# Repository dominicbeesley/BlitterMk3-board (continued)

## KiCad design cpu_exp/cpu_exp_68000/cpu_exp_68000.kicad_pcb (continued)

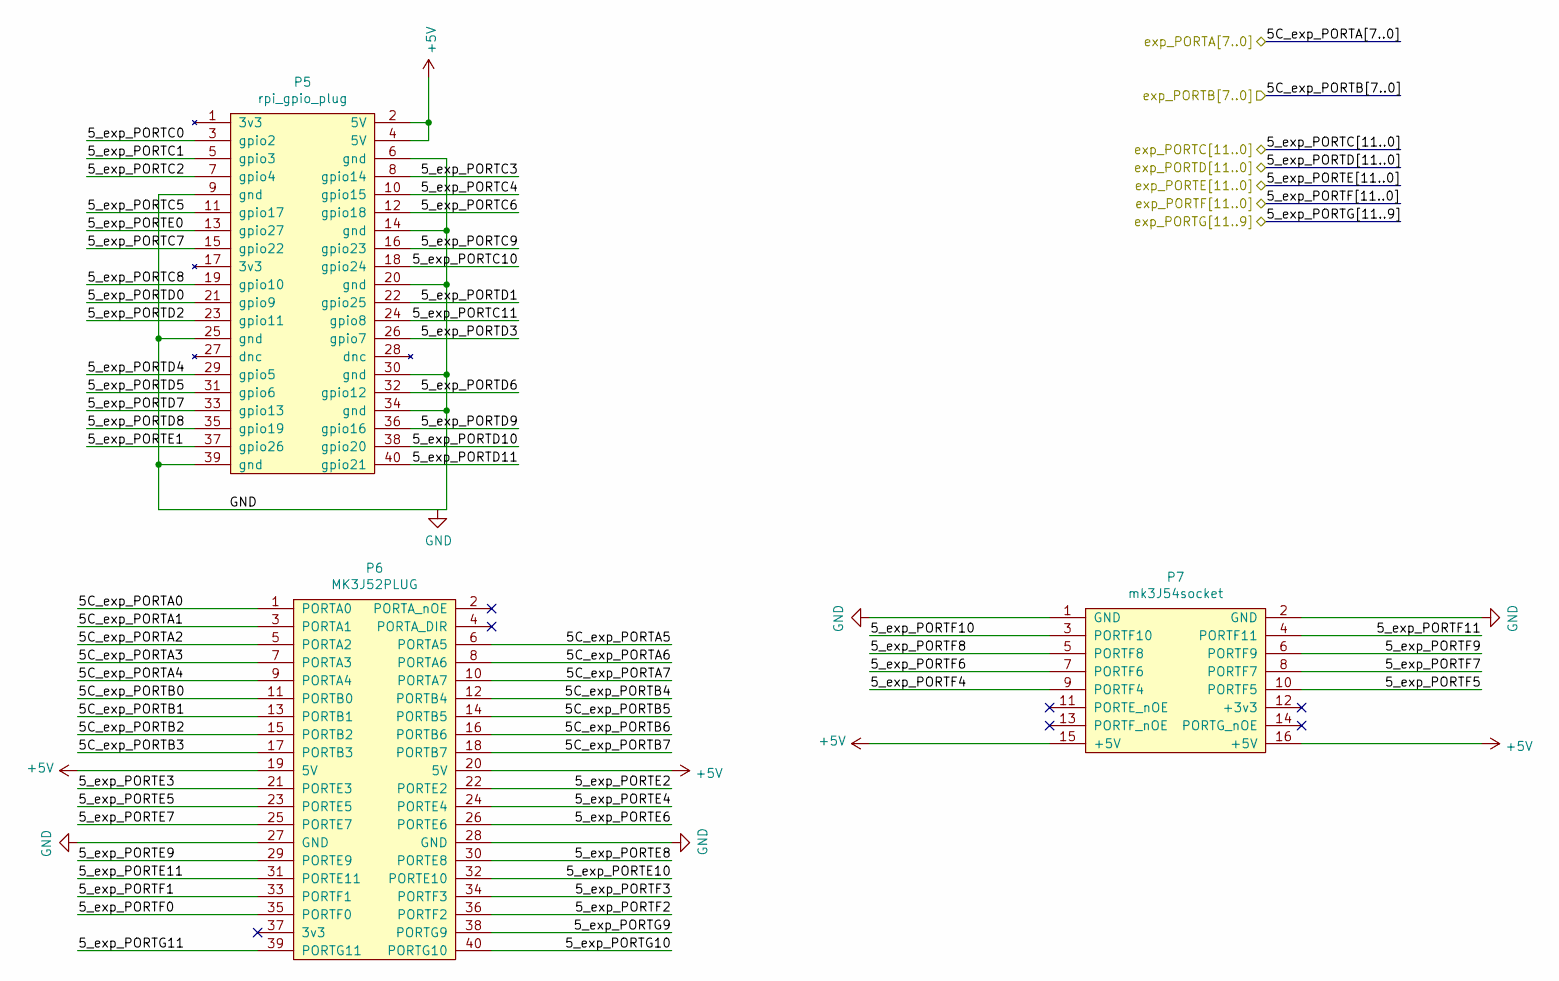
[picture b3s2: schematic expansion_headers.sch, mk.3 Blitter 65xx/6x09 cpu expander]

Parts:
P5: rpi_gpio_plug; PinHeader_2x20_P2.54mm_Vertical_SMD-dom
P6: MK3J52PLUG; PinSocket_2x20_P2.54mm_Vertical_SMD-dom
P7: mk3J54socket; PinSocket_2x08_P2.54mm_Vertical_SMD-dom

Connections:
+5V: P5.2 (5V), P5.4 (5V), P6.19 (5V), P6.20 (5V), P7.15 (+5V), P7.16 (+5V); also elsewhere on the board
/PORTA0: P6.1 (PORTA0); also elsewhere on the board
/PORTA1: P6.3 (PORTA1); also elsewhere on the board
/PORTA2: P6.5 (PORTA2); also elsewhere on the board
/PORTA3: P6.7 (PORTA3); also elsewhere on the board
/PORTA4: P6.9 (PORTA4); also elsewhere on the board
/PORTA5: P6.6 (PORTA5); also elsewhere on the board
/PORTA6: P6.8 (PORTA6); also elsewhere on the board
/PORTA7: P6.10 (PORTA7); also elsewhere on the board
/PORTB0: P6.11 (PORTB0); also elsewhere on the board
/PORTB1: P6.13 (PORTB1); also elsewhere on the board
/PORTB2: P6.15 (PORTB2); also elsewhere on the board
/PORTB3: P6.17 (PORTB3); also elsewhere on the board
/PORTB4: P6.12 (PORTB4); also elsewhere on the board
/PORTB5: P6.14 (PORTB5); also elsewhere on the board
/PORTB6: P6.16 (PORTB6); also elsewhere on the board
/PORTB7: P6.18 (PORTB7); also elsewhere on the board
/PORTC0: P5.3 (gpio2); also elsewhere on the board
/PORTC1: P5.5 (gpio3); also elsewhere on the board
/PORTC2: P5.7 (gpio4); also elsewhere on the board
/PORTC3: P5.8 (gpio14); also elsewhere on the board
/PORTC4: P5.10 (gpio15); also elsewhere on the board
/PORTC5: P5.11 (gpio17); also elsewhere on the board
/PORTC6: P5.12 (gpio18); also elsewhere on the board
/PORTC7: P5.15 (gpio22); also elsewhere on the board
/PORTC8: P5.19 (gpio10); also elsewhere on the board
/PORTC9: P5.16 (gpio23); also elsewhere on the board
/PORTC10: P5.18 (gpio24); also elsewhere on the board
/PORTC11: P5.24 (gpio8); also elsewhere on the board
/PORTD0: P5.21 (gpio9); also elsewhere on the board
/PORTD1: P5.22 (gpio25); also elsewhere on the board
/PORTD2: P5.23 (gpio11); also elsewhere on the board
/PORTD3: P5.26 (gpio7); also elsewhere on the board
/PORTD4: P5.29 (gpio5); also elsewhere on the board
/PORTD5: P5.31 (gpio6); also elsewhere on the board
/PORTD6: P5.32 (gpio12); also elsewhere on the board
/PORTD7: P5.33 (gpio13); also elsewhere on the board
/PORTD8: P5.35 (gpio19); also elsewhere on the board
/PORTD9: P5.36 (gpio16); also elsewhere on the board
/PORTD10: P5.38 (gpio20); also elsewhere on the board
/PORTD11: P5.40 (gpio21); also elsewhere on the board
/PORTE0: P5.13 (gpio27); also elsewhere on the board
/PORTE1: P5.37 (gpio26); also elsewhere on the board
/PORTE2: P6.22 (PORTE2); also elsewhere on the board
/PORTE3: P6.21 (PORTE3); also elsewhere on the board
/PORTE4: P6.24 (PORTE4); also elsewhere on the board
/PORTE5: P6.23 (PORTE5); also elsewhere on the board
/PORTE6: P6.26 (PORTE6); also elsewhere on the board
/PORTE7: P6.25 (PORTE7); also elsewhere on the board
/PORTE8: P6.30 (PORTE8); also elsewhere on the board
/PORTE9: P6.29 (PORTE9); also elsewhere on the board
/PORTE10: P6.32 (PORTE10); also elsewhere on the board
/PORTE11: P6.31 (PORTE11); also elsewhere on the board
/PORTF0: P6.35 (PORTF0); also elsewhere on the board
/PORTF1: P6.33 (PORTF1); also elsewhere on the board
/PORTF2: P6.36 (PORTF2); also elsewhere on the board
/PORTF3: P6.34 (PORTF3); also elsewhere on the board
/PORTF4: P7.9 (PORTF4); also elsewhere on the board
/PORTF5: P7.10 (PORTF5); also elsewhere on the board
/PORTF6: P7.7 (PORTF6); also elsewhere on the board
/PORTF7: P7.8 (PORTF7); also elsewhere on the board
/PORTF8: P7.5 (PORTF8); also elsewhere on the board
/PORTF9: P7.6 (PORTF9); also elsewhere on the board
/PORTF10: P7.3 (PORTF10); also elsewhere on the board
/PORTF11: P7.4 (PORTF11); also elsewhere on the board
/PORTG9: P6.38 (PORTG9); also elsewhere on the board
/PORTG10: P6.40 (PORTG10); also elsewhere on the board
/PORTG11: P6.39 (PORTG11); also elsewhere on the board
GND: P5.6 (gnd), P5.9 (gnd), P5.14 (gnd), P5.20 (gnd), P5.25 (gnd), P5.30 (gnd), P5.34 (gnd), P5.39 (gnd), P6.27 (GND), P6.28 (GND), P7.1 (GND), P7.2 (GND); also elsewhere on the board

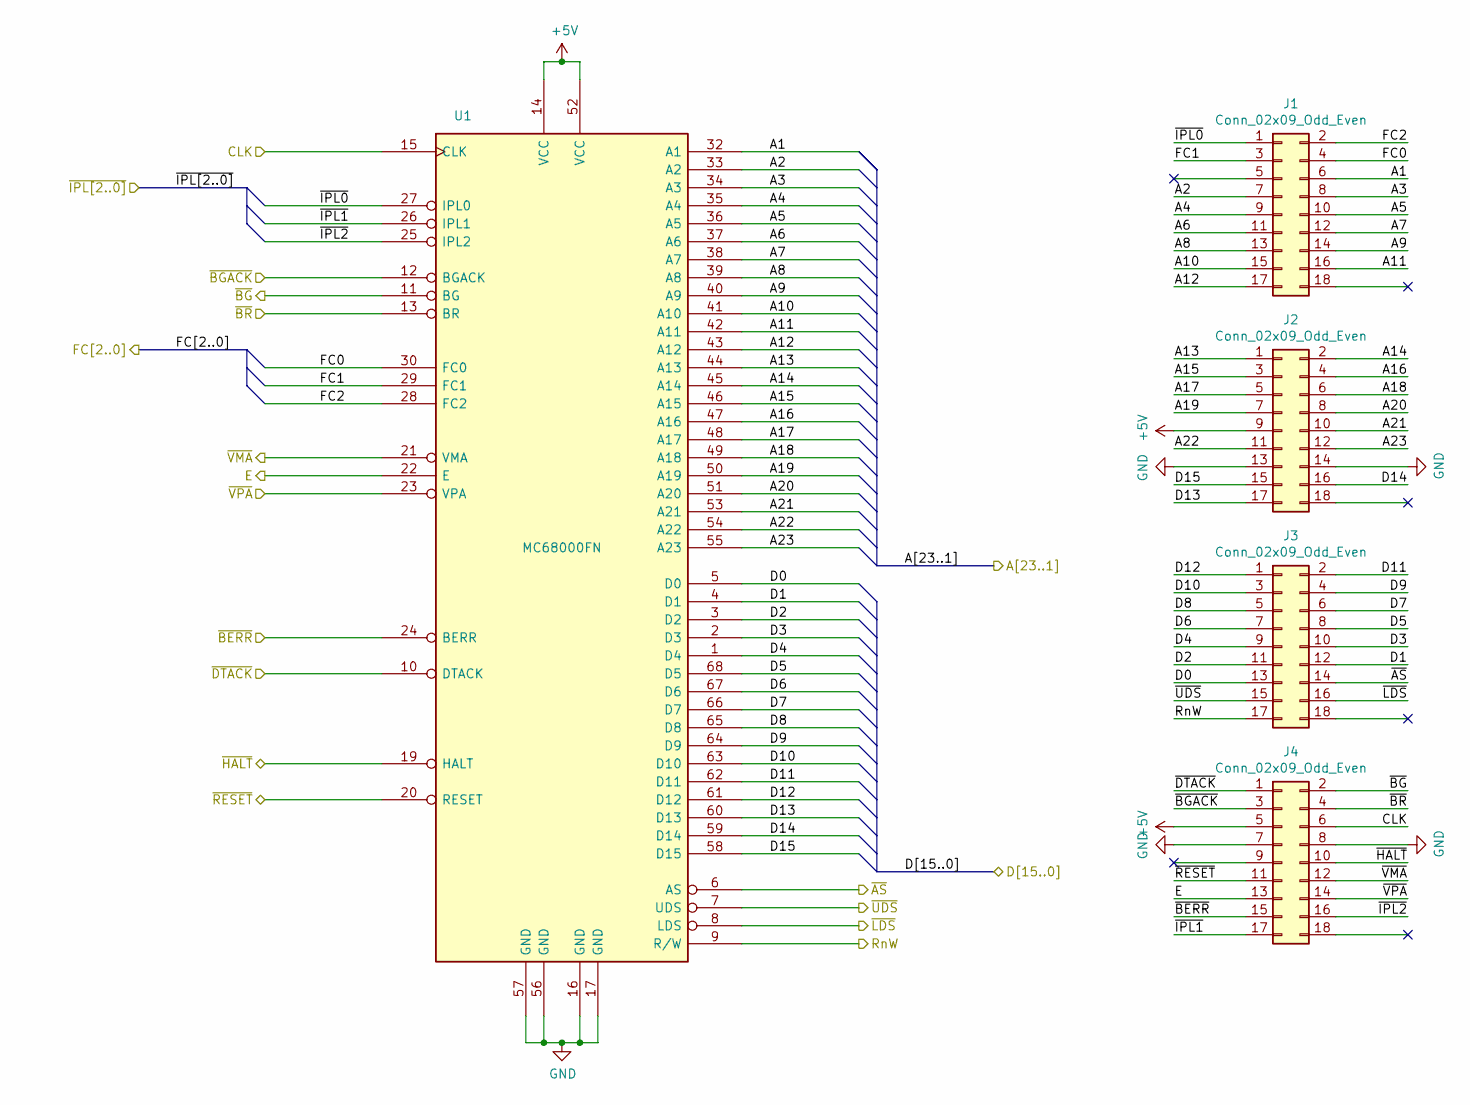
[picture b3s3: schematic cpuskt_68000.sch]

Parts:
J1, J2, J3, J4: Conn_02x09_Odd_Even; PinHeader_2x09_P2.54mm_Vertical_SMD-dom
U1: MC68000FN; PLCC-68_THT-Socket

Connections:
+5V: J2.9, J4.5, U1.14 (VCC), U1.52 (VCC); also elsewhere on the board
/PORTA0: J3.13, U1.5 (D0); also elsewhere on the board
/PORTA1: J3.12, U1.4 (D1); also elsewhere on the board
/PORTA2: J3.11, U1.3 (D2); also elsewhere on the board
/PORTA3: J3.10, U1.2 (D3); also elsewhere on the board
/PORTA4: J3.9, U1.1 (D4); also elsewhere on the board
/PORTA5: J3.8, U1.68 (D5); also elsewhere on the board
/PORTA6: J3.7, U1.67 (D6); also elsewhere on the board
/PORTA7: J3.6, U1.66 (D7); also elsewhere on the board
/PORTB0: J4.14, U1.23 (VPA); also elsewhere on the board
/PORTB1: J4.15, U1.24 (BERR); also elsewhere on the board
/PORTB2: J4.6, U1.15 (CLK); also elsewhere on the board
/PORTB3: J4.3, U1.12 (BGACK); also elsewhere on the board
/PORTB4: J4.17, U1.26 (IPL1); also elsewhere on the board
/PORTB5: J1.1, U1.27 (IPL0); also elsewhere on the board
/PORTB6: J4.16, U1.25 (IPL2); also elsewhere on the board
/PORTB7: J4.1, U1.10 (DTACK); also elsewhere on the board
/PORTC0: J3.16, U1.8 (LDS); also elsewhere on the board
/PORTC1: J1.6, U1.32 (A1); also elsewhere on the board
/PORTC2: J1.7, U1.33 (A2); also elsewhere on the board
/PORTC3: J1.8, U1.34 (A3); also elsewhere on the board
/PORTC4: J1.9, U1.35 (A4); also elsewhere on the board
/PORTC5: J1.10, U1.36 (A5); also elsewhere on the board
/PORTC6: J1.11, U1.37 (A6); also elsewhere on the board
/PORTC7: J1.12, U1.38 (A7); also elsewhere on the board
/PORTC8: J2.4, U1.47 (A16); also elsewhere on the board
/PORTC9: J2.5, U1.48 (A17); also elsewhere on the board
/PORTC10: J2.6, U1.49 (A18); also elsewhere on the board
/PORTC11: J2.7, U1.50 (A19); also elsewhere on the board
/PORTD0: J4.13, U1.22 (E); also elsewhere on the board
/PORTD1: J3.17, U1.9 (R/W); also elsewhere on the board
/PORTD2: J3.15, U1.7 (UDS); also elsewhere on the board
/PORTD3: J1.4, U1.30 (FC0); also elsewhere on the board
/PORTD4: J1.2, U1.28 (FC2); also elsewhere on the board
/PORTD5: J3.14, U1.6 (AS); also elsewhere on the board
/PORTD6: J1.3, U1.29 (FC1); also elsewhere on the board
/PORTD7: J4.2, U1.11 (BG); also elsewhere on the board
/PORTD8: J4.4, U1.13 (BR); also elsewhere on the board
/PORTD9: J4.11, U1.20 (RESET); also elsewhere on the board
/PORTD10: J4.10, U1.19 (HALT); also elsewhere on the board
/PORTD11: J4.12, U1.21 (VMA); also elsewhere on the board
/PORTE0: J1.13, U1.39 (A8); also elsewhere on the board
/PORTE1: J1.14, U1.40 (A9); also elsewhere on the board
/PORTE2: J1.15, U1.41 (A10); also elsewhere on the board
/PORTE3: J1.16, U1.42 (A11); also elsewhere on the board
/PORTE4: J1.17, U1.43 (A12); also elsewhere on the board
/PORTE5: J2.1, U1.44 (A13); also elsewhere on the board
/PORTE6: J2.2, U1.45 (A14); also elsewhere on the board
/PORTE7: J2.3, U1.46 (A15); also elsewhere on the board
/PORTE8: J2.8, U1.51 (A20); also elsewhere on the board
/PORTE9: J2.10, U1.53 (A21); also elsewhere on the board
/PORTE10: J2.11, U1.54 (A22); also elsewhere on the board
/PORTE11: J2.12, U1.55 (A23); also elsewhere on the board
/PORTF4: J3.5, U1.65 (D8); also elsewhere on the board
/PORTF5: J3.4, U1.64 (D9); also elsewhere on the board
/PORTF6: J3.3, U1.63 (D10); also elsewhere on the board
/PORTF7: J3.2, U1.62 (D11); also elsewhere on the board
/PORTF8: J3.1, U1.61 (D12); also elsewhere on the board
/PORTF9: J2.17, U1.60 (D13); also elsewhere on the board
/PORTF10: J2.16, U1.59 (D14); also elsewhere on the board
/PORTF11: J2.15, U1.58 (D15); also elsewhere on the board
GND: J2.13, J2.14, J4.7, J4.8, U1.16 (GND), U1.17 (GND), U1.56 (GND), U1.57 (GND); also elsewhere on the board

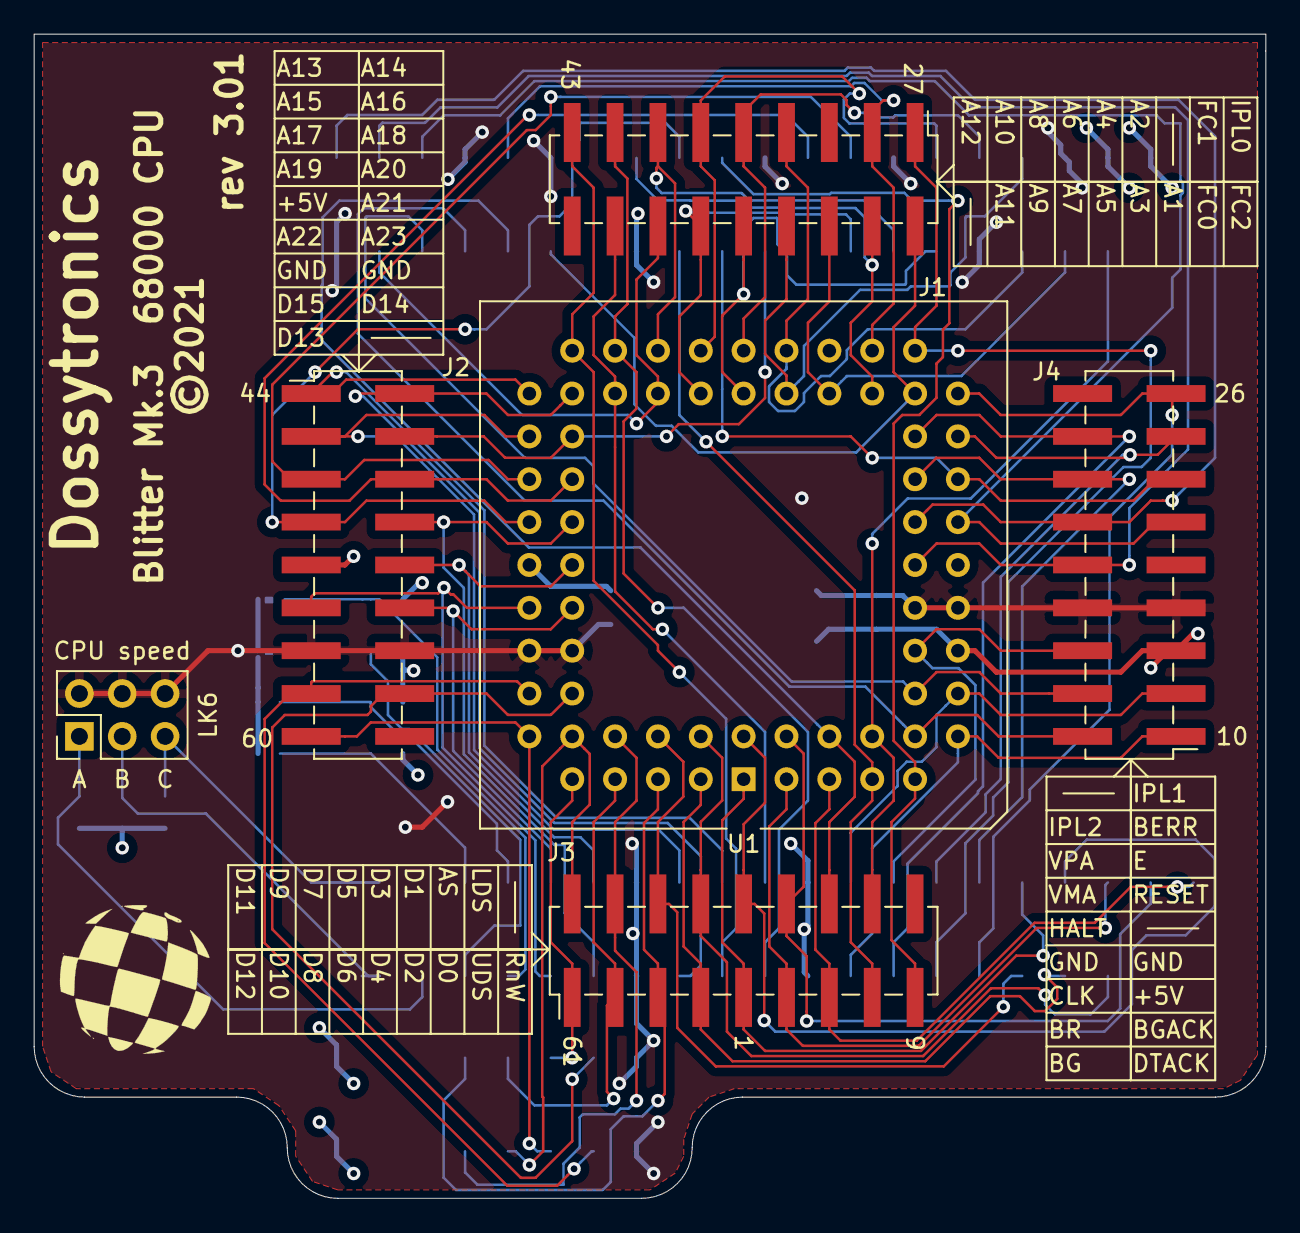
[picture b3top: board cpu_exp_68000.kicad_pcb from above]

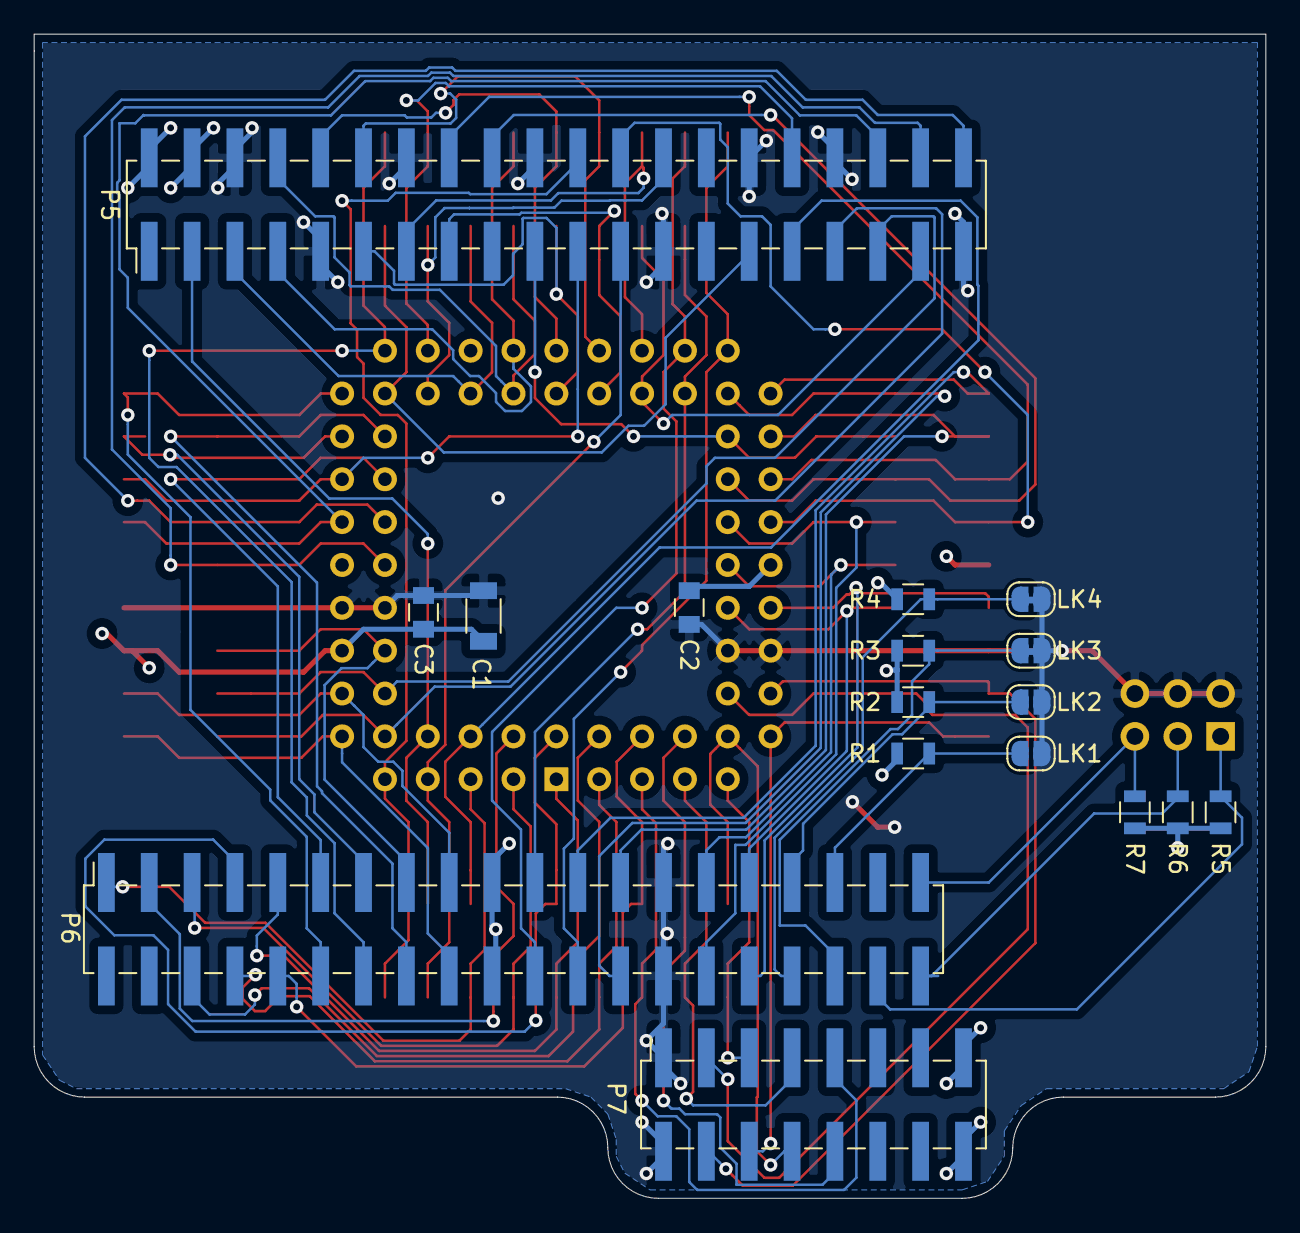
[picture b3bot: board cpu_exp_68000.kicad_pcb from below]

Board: 4 copper layers, 73.0 x 69.0 mm, 23 parts (17 on the bottom side), 69 nets.

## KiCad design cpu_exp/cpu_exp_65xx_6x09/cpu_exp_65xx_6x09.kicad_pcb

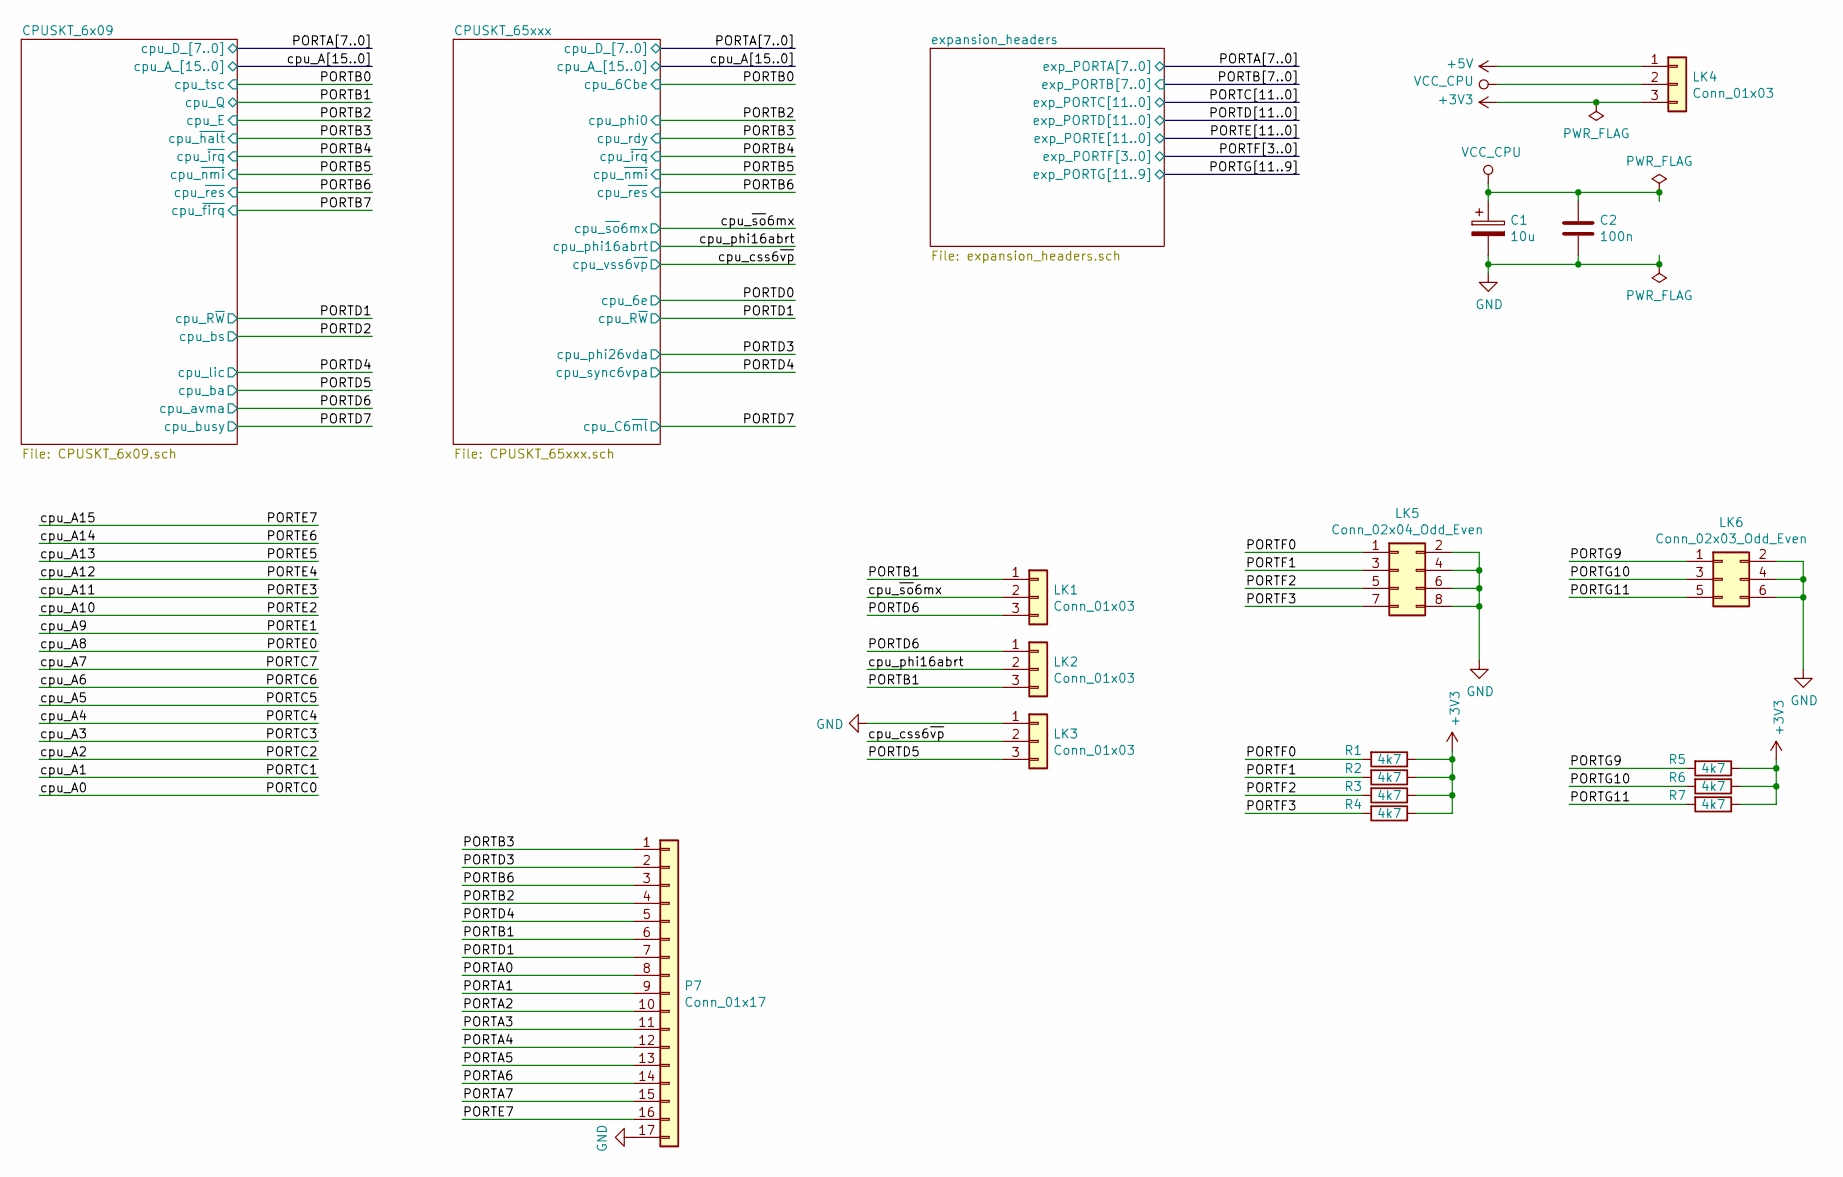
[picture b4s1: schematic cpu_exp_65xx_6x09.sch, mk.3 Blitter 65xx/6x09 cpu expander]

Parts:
C1: 10u; C_1206
C2: 100n; C_1206
LK1, LK2, LK3, LK4: Conn_01x03; PinHeader_1x03_P2.54mm_Vertical
LK5: Conn_02x04_Odd_Even; PinHeader_2x04_P2.54mm_Vertical
LK6: Conn_02x03_Odd_Even; PinHeader_2x03_P2.54mm_Vertical
P7: Conn_01x17; PinHeader_1x17_P2.54mm_Vertical
R1, R2, R3, R4, R5, R6, R7: 4k7; R_1206

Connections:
+3V3: LK4.3, R1.1, R2.1, R3.1, R4.1, R5.1, R6.1, R7.1; also elsewhere on the board
+5V: LK4.1; also elsewhere on the board
/PORTA0: P7.8; also elsewhere on the board
/PORTA1: P7.9; also elsewhere on the board
/PORTA2: P7.10; also elsewhere on the board
/PORTA3: P7.11; also elsewhere on the board
/PORTA4: P7.12; also elsewhere on the board
/PORTA5: P7.13; also elsewhere on the board
/PORTA6: P7.14; also elsewhere on the board
/PORTA7: P7.15; also elsewhere on the board
/PORTB1: LK1.1, LK2.3, P7.6; also elsewhere on the board
/PORTB2: P7.4; also elsewhere on the board
/PORTB3: P7.1; also elsewhere on the board
/PORTB6: P7.3; also elsewhere on the board
/PORTD1: P7.7; also elsewhere on the board
/PORTD3: P7.2; also elsewhere on the board
/PORTD4: P7.5; also elsewhere on the board
/PORTD5: LK3.3; also elsewhere on the board
/PORTD6: LK1.3, LK2.1; also elsewhere on the board
/PORTE7: P7.16; also elsewhere on the board
/PORTF0: LK5.1, R1.2; also elsewhere on the board
/PORTF1: LK5.3, R2.2; also elsewhere on the board
/PORTF2: LK5.5, R3.2; also elsewhere on the board
/PORTF3: LK5.7, R4.2; also elsewhere on the board
/PORTG9: LK6.1, R5.2; also elsewhere on the board
/PORTG10: LK6.3, R6.2; also elsewhere on the board
/PORTG11: LK6.5, R7.2; also elsewhere on the board
/cpu_css6~vp: LK3.2; also elsewhere on the board
/cpu_phi16abrt: LK2.2; also elsewhere on the board
/cpu_~so~6mx: LK1.2; also elsewhere on the board
GND: C1.2, C2.2, LK3.1, LK5.2, LK5.4, LK5.6, LK5.8, LK6.2, LK6.4, LK6.6, P7.17; also elsewhere on the board
VCC_CPU: C1.1, C2.1, LK4.2; also elsewhere on the board

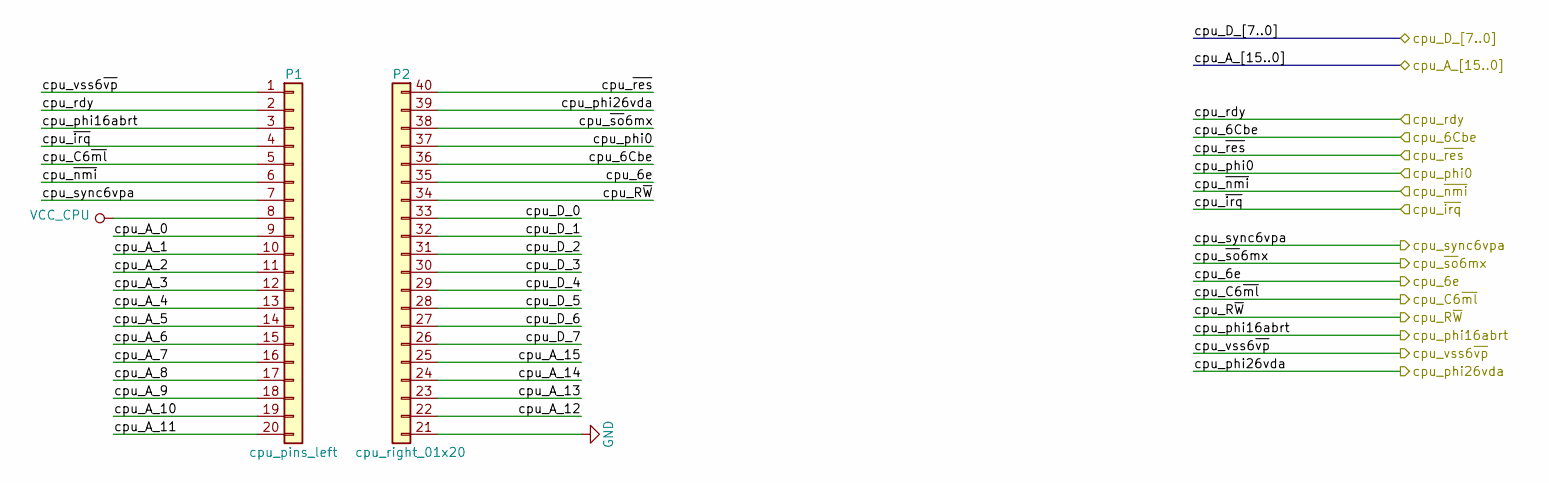
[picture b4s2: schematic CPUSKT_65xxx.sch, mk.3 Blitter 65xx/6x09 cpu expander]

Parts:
P1: cpu_pins_left; PinSocket_1x20_P2.54mm_Vertical
P2: cpu_right_01x20; Pin_Header_Straight_1x20_Pitch2.54mm_21_40

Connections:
/PORTA0: P2.33; also elsewhere on the board
/PORTA1: P2.32; also elsewhere on the board
/PORTA2: P2.31; also elsewhere on the board
/PORTA3: P2.30; also elsewhere on the board
/PORTA4: P2.29; also elsewhere on the board
/PORTA5: P2.28; also elsewhere on the board
/PORTA6: P2.27; also elsewhere on the board
/PORTA7: P2.26; also elsewhere on the board
/PORTB0: P2.36; also elsewhere on the board
/PORTB2: P2.37; also elsewhere on the board
/PORTB3: P1.2; also elsewhere on the board
/PORTB4: P1.4; also elsewhere on the board
/PORTB5: P1.6; also elsewhere on the board
/PORTB6: P2.40; also elsewhere on the board
/PORTC0: P1.9; also elsewhere on the board
/PORTC1: P1.10; also elsewhere on the board
/PORTC2: P1.11; also elsewhere on the board
/PORTC3: P1.12; also elsewhere on the board
/PORTC4: P1.13; also elsewhere on the board
/PORTC5: P1.14; also elsewhere on the board
/PORTC6: P1.15; also elsewhere on the board
/PORTC7: P1.16; also elsewhere on the board
/PORTD0: P2.35; also elsewhere on the board
/PORTD1: P2.34; also elsewhere on the board
/PORTD3: P2.39; also elsewhere on the board
/PORTD4: P1.7; also elsewhere on the board
/PORTD7: P1.5; also elsewhere on the board
/PORTE0: P1.17; also elsewhere on the board
/PORTE1: P1.18; also elsewhere on the board
/PORTE2: P1.19; also elsewhere on the board
/PORTE3: P1.20; also elsewhere on the board
/PORTE4: P2.22; also elsewhere on the board
/PORTE5: P2.23; also elsewhere on the board
/PORTE6: P2.24; also elsewhere on the board
/PORTE7: P2.25; also elsewhere on the board
/cpu_css6~vp: P1.1; also elsewhere on the board
/cpu_phi16abrt: P1.3; also elsewhere on the board
/cpu_~so~6mx: P2.38; also elsewhere on the board
GND: P2.21; also elsewhere on the board
VCC_CPU: P1.8; also elsewhere on the board

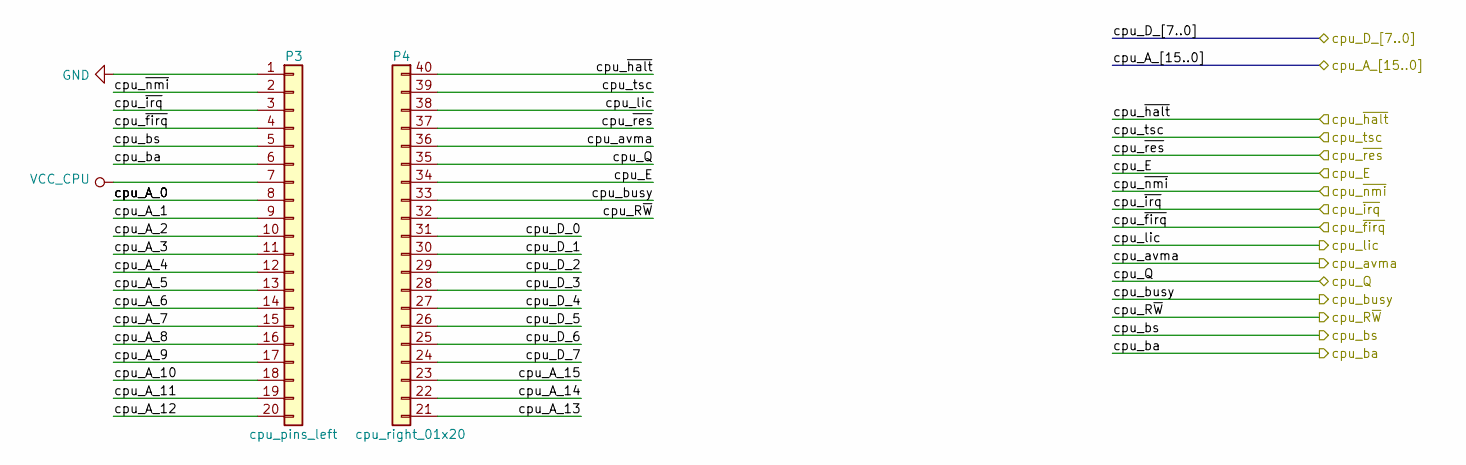
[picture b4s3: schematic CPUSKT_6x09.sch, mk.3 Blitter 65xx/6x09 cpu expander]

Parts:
P3: cpu_pins_left; PinSocket_1x20_P2.54mm_Vertical
P4: cpu_right_01x20; Pin_Header_Straight_1x20_Pitch2.54mm_21_40

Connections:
/PORTA0: P4.31; also elsewhere on the board
/PORTA1: P4.30; also elsewhere on the board
/PORTA2: P4.29; also elsewhere on the board
/PORTA3: P4.28; also elsewhere on the board
/PORTA4: P4.27; also elsewhere on the board
/PORTA5: P4.26; also elsewhere on the board
/PORTA6: P4.25; also elsewhere on the board
/PORTA7: P4.24; also elsewhere on the board
/PORTB0: P4.39; also elsewhere on the board
/PORTB1: P4.35; also elsewhere on the board
/PORTB2: P4.34; also elsewhere on the board
/PORTB3: P4.40; also elsewhere on the board
/PORTB4: P3.3; also elsewhere on the board
/PORTB5: P3.2; also elsewhere on the board
/PORTB6: P4.37; also elsewhere on the board
/PORTB7: P3.4; also elsewhere on the board
/PORTC0: P3.8; also elsewhere on the board
/PORTC1: P3.9; also elsewhere on the board
/PORTC2: P3.10; also elsewhere on the board
/PORTC3: P3.11; also elsewhere on the board
/PORTC4: P3.12; also elsewhere on the board
/PORTC5: P3.13; also elsewhere on the board
/PORTC6: P3.14; also elsewhere on the board
/PORTC7: P3.15; also elsewhere on the board
/PORTD1: P4.32; also elsewhere on the board
/PORTD2: P3.5; also elsewhere on the board
/PORTD4: P4.38; also elsewhere on the board
/PORTD5: P3.6; also elsewhere on the board
/PORTD6: P4.36; also elsewhere on the board
/PORTD7: P4.33; also elsewhere on the board
/PORTE0: P3.16; also elsewhere on the board
/PORTE1: P3.17; also elsewhere on the board
/PORTE2: P3.18; also elsewhere on the board
/PORTE3: P3.19; also elsewhere on the board
/PORTE4: P3.20; also elsewhere on the board
/PORTE5: P4.21; also elsewhere on the board
/PORTE6: P4.22; also elsewhere on the board
/PORTE7: P4.23; also elsewhere on the board
GND: P3.1; also elsewhere on the board
VCC_CPU: P3.7; also elsewhere on the board

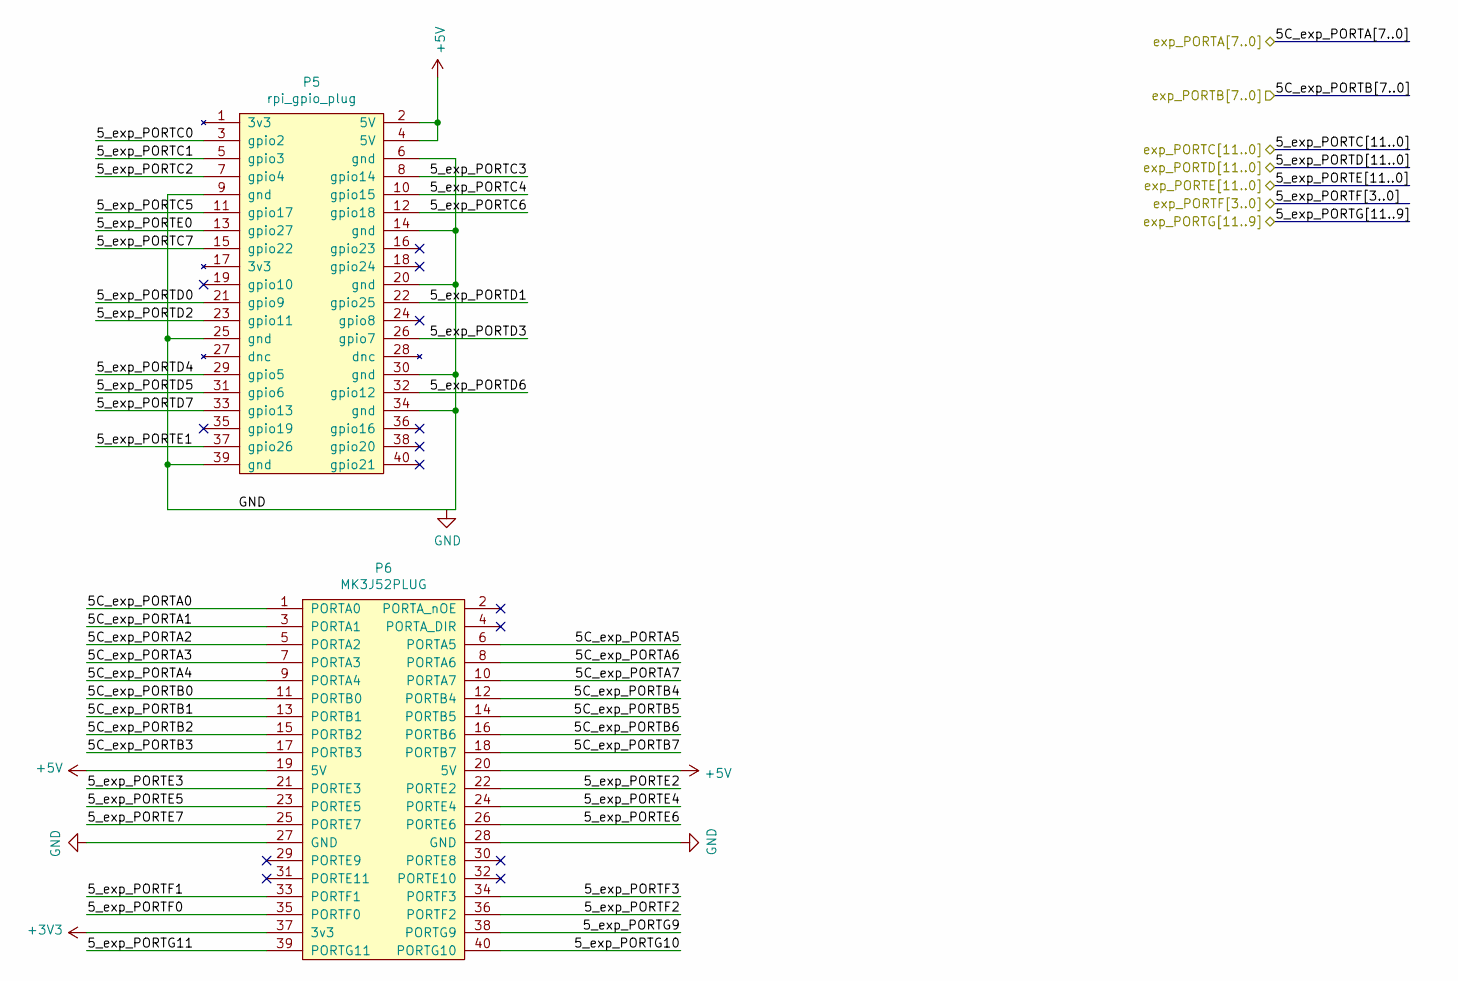
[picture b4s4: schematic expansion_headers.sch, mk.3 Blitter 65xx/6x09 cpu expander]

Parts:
P5: rpi_gpio_plug; PinHeader_2x20_P2.54mm_Vertical_SMD-dom
P6: MK3J52PLUG; PinSocket_2x20_P2.54mm_Vertical_SMD-dom

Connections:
+3V3: P6.37 (3v3); also elsewhere on the board
+5V: P5.2 (5V), P5.4 (5V), P6.19 (5V), P6.20 (5V); also elsewhere on the board
/PORTA0: P6.1 (PORTA0); also elsewhere on the board
/PORTA1: P6.3 (PORTA1); also elsewhere on the board
/PORTA2: P6.5 (PORTA2); also elsewhere on the board
/PORTA3: P6.7 (PORTA3); also elsewhere on the board
/PORTA4: P6.9 (PORTA4); also elsewhere on the board
/PORTA5: P6.6 (PORTA5); also elsewhere on the board
/PORTA6: P6.8 (PORTA6); also elsewhere on the board
/PORTA7: P6.10 (PORTA7); also elsewhere on the board
/PORTB0: P6.11 (PORTB0); also elsewhere on the board
/PORTB1: P6.13 (PORTB1); also elsewhere on the board
/PORTB2: P6.15 (PORTB2); also elsewhere on the board
/PORTB3: P6.17 (PORTB3); also elsewhere on the board
/PORTB4: P6.12 (PORTB4); also elsewhere on the board
/PORTB5: P6.14 (PORTB5); also elsewhere on the board
/PORTB6: P6.16 (PORTB6); also elsewhere on the board
/PORTB7: P6.18 (PORTB7); also elsewhere on the board
/PORTC0: P5.3 (gpio2); also elsewhere on the board
/PORTC1: P5.5 (gpio3); also elsewhere on the board
/PORTC2: P5.7 (gpio4); also elsewhere on the board
/PORTC3: P5.8 (gpio14); also elsewhere on the board
/PORTC4: P5.10 (gpio15); also elsewhere on the board
/PORTC5: P5.11 (gpio17); also elsewhere on the board
/PORTC6: P5.12 (gpio18); also elsewhere on the board
/PORTC7: P5.15 (gpio22); also elsewhere on the board
/PORTD0: P5.21 (gpio9); also elsewhere on the board
/PORTD1: P5.22 (gpio25); also elsewhere on the board
/PORTD2: P5.23 (gpio11); also elsewhere on the board
/PORTD3: P5.26 (gpio7); also elsewhere on the board
/PORTD4: P5.29 (gpio5); also elsewhere on the board
/PORTD5: P5.31 (gpio6); also elsewhere on the board
/PORTD6: P5.32 (gpio12); also elsewhere on the board
/PORTD7: P5.33 (gpio13); also elsewhere on the board
/PORTE0: P5.13 (gpio27); also elsewhere on the board
/PORTE1: P5.37 (gpio26); also elsewhere on the board
/PORTE2: P6.22 (PORTE2); also elsewhere on the board
/PORTE3: P6.21 (PORTE3); also elsewhere on the board
/PORTE4: P6.24 (PORTE4); also elsewhere on the board
/PORTE5: P6.23 (PORTE5); also elsewhere on the board
/PORTE6: P6.26 (PORTE6); also elsewhere on the board
/PORTE7: P6.25 (PORTE7); also elsewhere on the board
/PORTF0: P6.35 (PORTF0); also elsewhere on the board
/PORTF1: P6.33 (PORTF1); also elsewhere on the board
/PORTF2: P6.36 (PORTF2); also elsewhere on the board
/PORTF3: P6.34 (PORTF3); also elsewhere on the board
/PORTG9: P6.38 (PORTG9); also elsewhere on the board
/PORTG10: P6.40 (PORTG10); also elsewhere on the board
/PORTG11: P6.39 (PORTG11); also elsewhere on the board
GND: P5.6 (gnd), P5.9 (gnd), P5.14 (gnd), P5.20 (gnd), P5.25 (gnd), P5.30 (gnd), P5.34 (gnd), P5.39 (gnd), P6.27 (GND), P6.28 (GND); also elsewhere on the board
